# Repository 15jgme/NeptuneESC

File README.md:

# NeptuneESC
The goal of this project is to create the smallest possible electronic speed controller module for a single motor. This work is essentially Blue Robotic's BlueESC with a different, smaller, board layout. 

## Quick notes
* Design in KiCad
* ATmega8A-AU MCU
* I2C operations
* 5cm x 3cm size
* Programmable ESC

## Layout

The design is made to be compatable with assembly and board fabrication from [JLCPCB]https://jlcpcb.com/

The current size is about 5cm by 2cm in a single PCB, and is designed to support motors used in midsized UAV applications.

## Usage

As with the BlueESC, Neptune operates on [tgy](https://github.com/bluerobotics/tgy) firmware and can be run off of an I2C connection, making it ideal for daisychaining and tinkering. Note that since this project was in active development tgy is no longer maintained, but the atmega8a-au should allow for a variety of different firmware if desired. 

## State

This project was never assembled, however it is nearly complete. Anyone who needs something similar should have no trouble completing it!
Here's whats left before completion.

* Layout J8 and J7
* Finish about 10 traces and add ground and power planes as desired
* Make better A/B/C channel pads and connectors.
* Electrical checks
* _Fab it!_

If I need a custom ESC I'll continue work on this but until then it's for anyone who can make use of it. Cheers 🍻

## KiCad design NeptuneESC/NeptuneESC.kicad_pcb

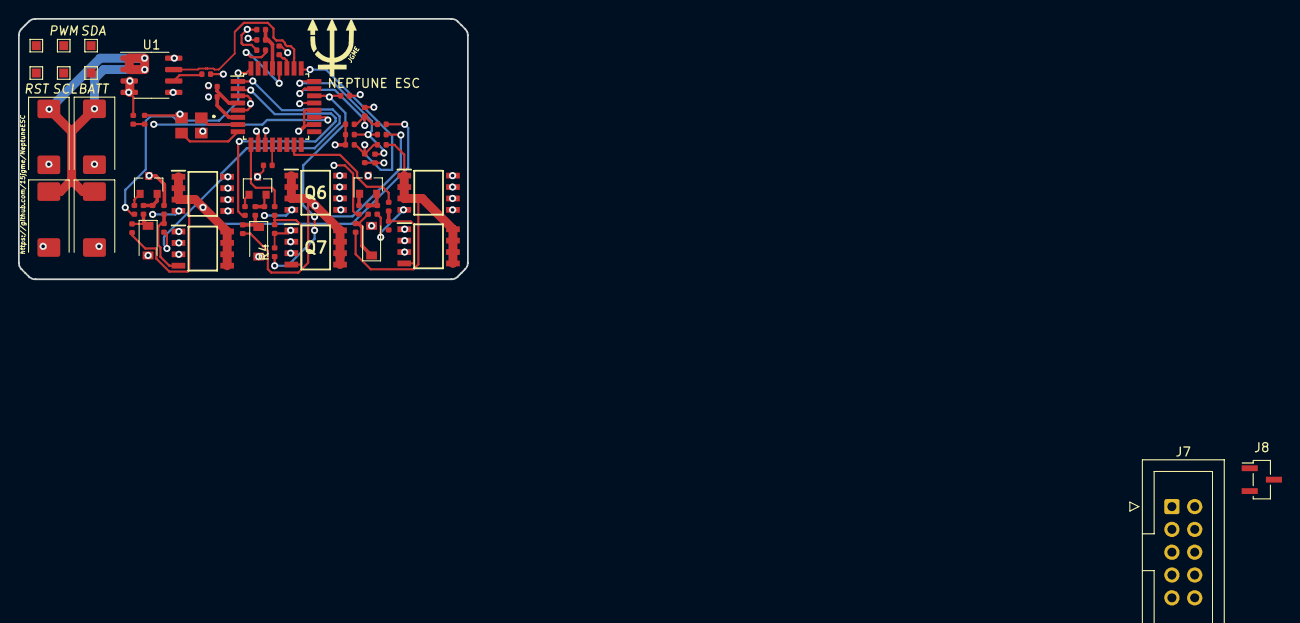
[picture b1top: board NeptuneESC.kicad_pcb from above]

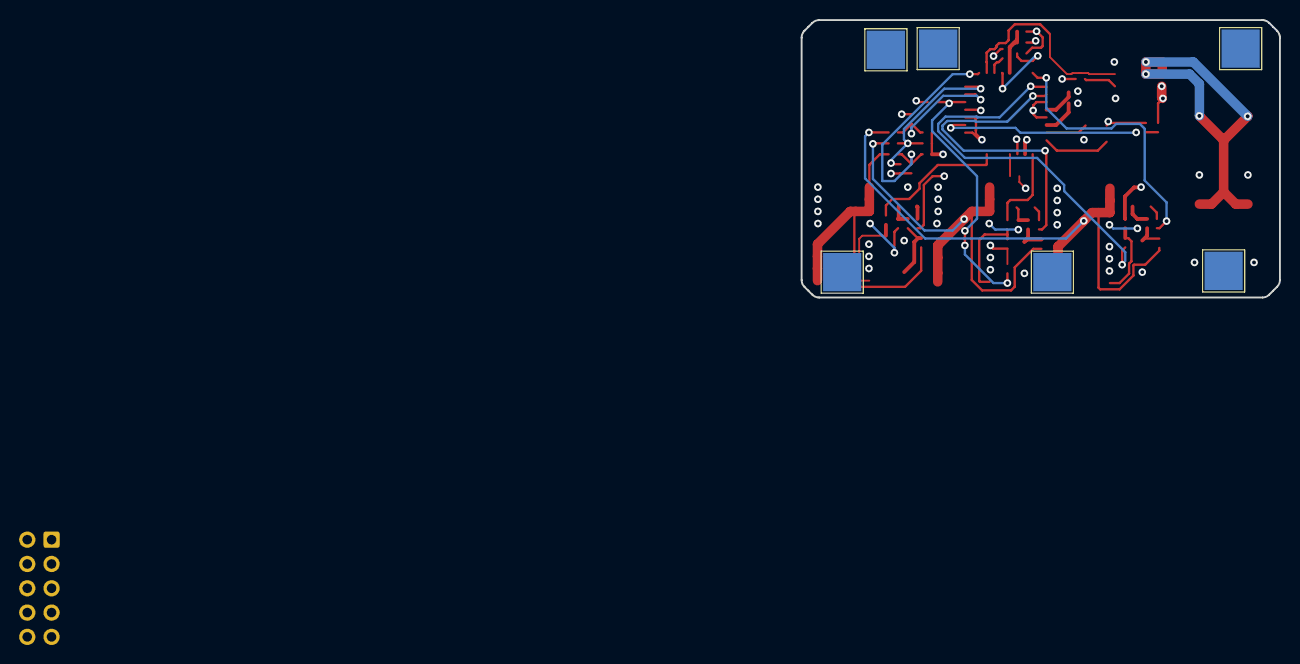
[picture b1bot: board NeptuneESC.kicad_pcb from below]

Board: 4 copper layers, 50.0 x 29.0 mm, 73 parts (6 on the bottom side), 46 nets.

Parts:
C1, C2, C3, C4: 100uF; CP_EIA-7343-43_Kemet-X
C5, C7, C8: 0.1uF; C_0402_1005Metric
C6: 1nF; C_0402_1005Metric
C9, C10, C11: C_Small; C_0402_1005Metric
D1, D2, D3: D_Schottky; D_SOD-123
J1, J2, J3, J4, J5, J6: Conn_01x01_Female; TestPoint_Pad_4.0x4.0mm
J7: AVR-ISP-10; IDC-Header_2x05_P2.54mm_Vertical
J8: Conn_01x03_Male; PinSocket_1x03_P1.27mm_Vertical_SMD_Pin1Left
J9, J10, J11, J12, J13, J14: Conn_01x01_Female; TestPoint_Pad_1.0x1.0mm
L1: Neptune; neptuneLogo
Q1, Q2, Q3: Q_NPN_BCE; SOT-23
Q4, Q5, Q6, Q7, Q8, Q9: AO4407A; SOIC127P600X175-8N
R1: 470k; R_0402_1005Metric
R2, R5, R6, R21, R26, R31: 10k; R_0402_1005Metric
R3, R8: 3.3k; R_0402_1005Metric
R4: 10k NTC; R_0402_1005Metric
R7: 18k; R_0402_1005Metric
R9, R10, R11, R15, R16, R17: 47k; R_0402_1005Metric
R12, R13, R14, R18, R23, R28: 4.7k; R_0402_1005Metric
R19, R22, R24, R27, R29, R32: 100; R_0402_1005Metric
R20, R25, R30: 2.2k; R_0402_1005Metric
U1: ACS712xLCTR-20A; SOIC-8_3.9x4.9mm_P1.27mm
U2: ATmega8A-AU; TQFP-32_7x7mm_P0.8mm
Y1: 16MHz; X322516MLB4SI

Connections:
+5V: C7.1, C8.1, J7.2, R2.1, R3.1, R5.1, R6.1, U1.8, U2.4, U2.6, U2.18, U2.20
+BATT: C1.1, C2.1, C3.1, C4.1, J1.1, J6.1, J9.1, J14.1, U1.1, U1.2
/MosfetArray/Gate-AH: Q4.4, R22.1
/MosfetArray/Gate-AL: Q5.4, R19.1, R21.2
/MosfetArray/Gate-BH: Q6.4, R27.1
/MosfetArray/Gate-BL: Q7.4, R24.1, R26.2
/MosfetArray/Gate-CH: Q8.4, R32.1
/MosfetArray/Gate-CL: Q9.4, R29.1, R31.2
A-Sense: R9.1, R12.1, R15.2, U2.23
B-Sense: R10.1, R13.1, R16.2, U2.24
C-Sense: R11.1, R14.1, R17.2, U2.25
CLK: J7.7, U2.17
Center: R9.2, R10.2, R11.2, U2.10
Current-Sig: U1.7, U2.26
GND: C1.2, C2.2, C3.2, C4.2, C5.2, C6.2, C7.2, C8.2, J7.4, J7.6, J7.8, J7.10, J8.1, Q1.3, Q2.3, Q3.3, Q5.1, Q5.2, Q5.3, Q7.1, Q7.2, Q7.3, Q9.1, Q9.2, Q9.3, R1.2, R4.2, R8.2, R12.2, R13.2, R14.2, R21.1, R26.1, R31.1, U1.5, U2.3, U2.5, U2.21, Y1.2
MISO: J7.9, U2.16
unnamed: C6.1, U1.6
unnamed: C9.2, D1.1, R20.1
unnamed: C10.2, D2.1, R25.1
unnamed: C11.2, D3.1, R30.1
unnamed: Q1.1, R18.1
unnamed: Q1.2, R20.2, R22.2
unnamed: Q2.1, R23.1
unnamed: Q2.2, R25.2, R27.2
unnamed: Q3.1, R28.1
unnamed: Q3.2, R30.2, R32.2
unnamed: U2.7, Y1.1
unnamed: U2.8, Y1.3
PWM: J3.1, J11.1, R1.1, U2.12
PWM-AH: R18.2, U2.32
PWM-AL: R19.2, U2.1
PWM-BH: R23.2, U2.2
PWM-BL: R24.2, U2.9
PWM-CH: R28.2, U2.11
PWM-CL: R29.2, U2.15
Phase-A: C9.1, Q4.1, Q4.2, Q4.3, Q5.5, Q5.6, Q5.7, Q5.8, R15.1
Phase-B: C10.1, Q6.1, Q6.2, Q6.3, Q7.5, Q7.6, Q7.7, Q7.8, R16.1
Phase-C: C11.1, Q8.1, Q8.2, Q8.3, Q9.5, Q9.6, Q9.7, Q9.8, R17.1
RST: C5.1, J2.1, J7.5, J10.1, R2.2, U2.29
RX: J8.3, U2.30
SCL: J4.1, J12.1, R5.2, U2.28
SDA: J5.1, J13.1, R6.2, U2.27
TX: J8.2, U2.31
Temp: R3.2, R4.1, U2.22
VBAT-signal: R7.2, R8.1, U2.19
Vdrive: D1.2, D2.2, D3.2, Q4.5, Q4.6, Q4.7, Q4.8, Q6.5, Q6.6, Q6.7, Q6.8, Q8.5, Q8.6, Q8.7, Q8.8, R7.1, U1.3, U1.4

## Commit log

2020-05-24 Kicad issues >:(
2020-05-27 Innitial layout
    Need to add motor pads
2021-07-18 adding some additional description
